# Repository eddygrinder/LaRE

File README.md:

## Objectives
This project is an integral part of the Master’s Dissertation entitled “LaRE – Expandable Remote Laboratory”.
It implements and manages a remote laboratory for electronics education, designed as a viable alternative to VISIR, with the additional commitment of being an open-source project, accessible to any educational institution regardless of geographical location.

The board matrix, the core element of the system, was developed based on a software-controlled architecture independent of proprietary platforms, ensuring that the system can be used without commercial licenses.

However, due to the current lack of support for the pyVirtualBench library on Linux systems and ARM architectures, the implementation of LaRE remains dependent on Windows systems — a factor that limits its adoption in more versatile and low-cost educational platforms.
Nevertheless, the modular architecture of LaRE enables future expansions and adaptations to different pedagogical contexts.

This dissertation partially fulfills the requirements defined in the Course Unit of Dissertation/Thesis of the 2nd year of the Master’s Degree in Electrical and Computer Engineering, specialization area in Automation and Systems.

## System Overview

The LaRE system is composed of:

* **PC (Server)** – runs a Flask-based Python web server.  
* **Raspberry Pi 5** – controls the relay matrix for switching circuits.  
* **NI VirtualBench (VB-8012)** – handles voltage, current, and waveform measurements.  
* **Web Interface** – implemented in HTML, CSS, and JavaScript for user interaction.  

Communication between the PC and Raspberry Pi is handled via **network sockets**, ensuring a simple and robust client–server connection.

## Helpful Resources
Flask base structure simplified and adapted to suit the project’s requirements.
* Some of the Flask features were inspired by a YouTube tutorial, which served as a reference for understanding the basic setup of routes, templates, and frontend communication - https://www.youtube.com/watch?v=dam0GPOAvVI
* https://flask.palletsprojects.com/en/stable/
* The pyVirtualBench library can be found here: https://github.com/armstrap/armstrap-pyvirtualbench
* Additional information: http://armstrap.org/2015/07/27/pyvirtualbench-controlling-five-instruments-from-a-single-python-application/

## Requirements (Windows Only)
* [NI VirtualBench hardware](http://www.ni.com/virtualbench/)
* [VirtualBench driver >= 1.1.0](https://www.ni.com/en-us/support/downloads/drivers/download.virtualbench-software.html#324215)
  Be sure to check "ANSI C Support" during installation.
    
* [Python >= 3.4](https://www.python.org/downloads/).  You will need 32-bit Python support to work with the NI-provided drivers.

## Dependencies
To install the Python dependencies:
* pip install -r requirements.txt

## Licensing
This project is distributed under the terms of the GNU General Public License, version 3 (GPLv3).
It includes portions of code adapted from: armstrap/armstrap-pyvirtualbench, licensed under the MIT License (© 2015 Charles Armstrap).

See the files LICENSE and THIRD_PARTY_LICENSES.txt for full details.

## Author
Eduardo Ramalhadeiro
Master’s in Electrical and Computer Engineering – Automation and Systems
Instituto Politécnico do Porto (ISEP)
© 2025

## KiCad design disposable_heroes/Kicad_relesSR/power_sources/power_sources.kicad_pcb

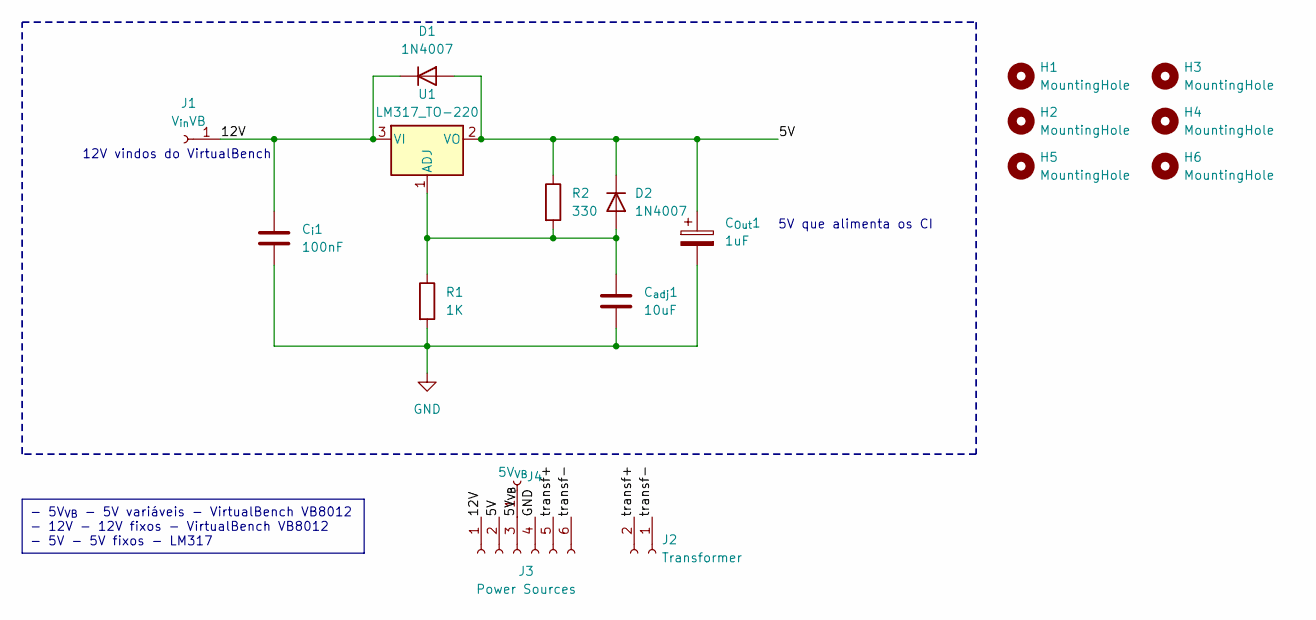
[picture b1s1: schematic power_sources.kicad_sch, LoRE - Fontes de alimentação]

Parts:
C_{Out}1: 1uF; CP_Radial_D5.0mm_P2.00mm
C_{adj}1: 10uF; CP_Radial_D5.0mm_P2.00mm
C_{i}1: 100nF; C_Disc_D5.1mm_W3.2mm_P5.00mm
D1, D2: 1N4007; D_DO-41_SOD81_P10.16mm_Horizontal
H1, H2, H3, H4, H5, H6: MountingHole; MountingHole_3.2mm_M3
J1: V_{in}VB; PinSocket_1x01_P2.54mm_Vertical
J2: Transformer; PinSocket_1x02_P2.54mm_Vertical
J3: Power Sources; PinSocket_1x06_P2.54mm_Vertical
J4: 5V_{VB}; PinSocket_1x01_P2.54mm_Vertical
R1: 1K; R_Axial_DIN0207_L6.3mm_D2.5mm_P15.24mm_Horizontal
R2: 330; R_Axial_DIN0207_L6.3mm_D2.5mm_P15.24mm_Horizontal
U1: LM317_TO-220; TO-220-3_Vertical

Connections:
/5V: C_{Out}1.1, D1.2 (A), D2.1 (K), J3.2, R2.1, U1.2 (VO)
/5V_{VB}: J3.3, J4.1
/12V: C_{i}1.1, D1.1 (K), J1.1, J3.1, U1.3 (VI)
/transf+: J2.2, J3.5
/transf-: J2.1, J3.6
GND: C_{Out}1.2, C_{adj}1.2, C_{i}1.2, J3.4, R1.2
unnamed: C_{adj}1.1, D2.2 (A), R1.1, R2.2, U1.1 (ADJ)

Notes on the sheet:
- 5V_{VB} - 5V variáveis - VirtualBench VB8012 - 12V - 12V fixos - VirtualBench VB8012 - 5V - 5V fixos - LM317
5V que alimenta os CI
12V vindos do VirtualBench

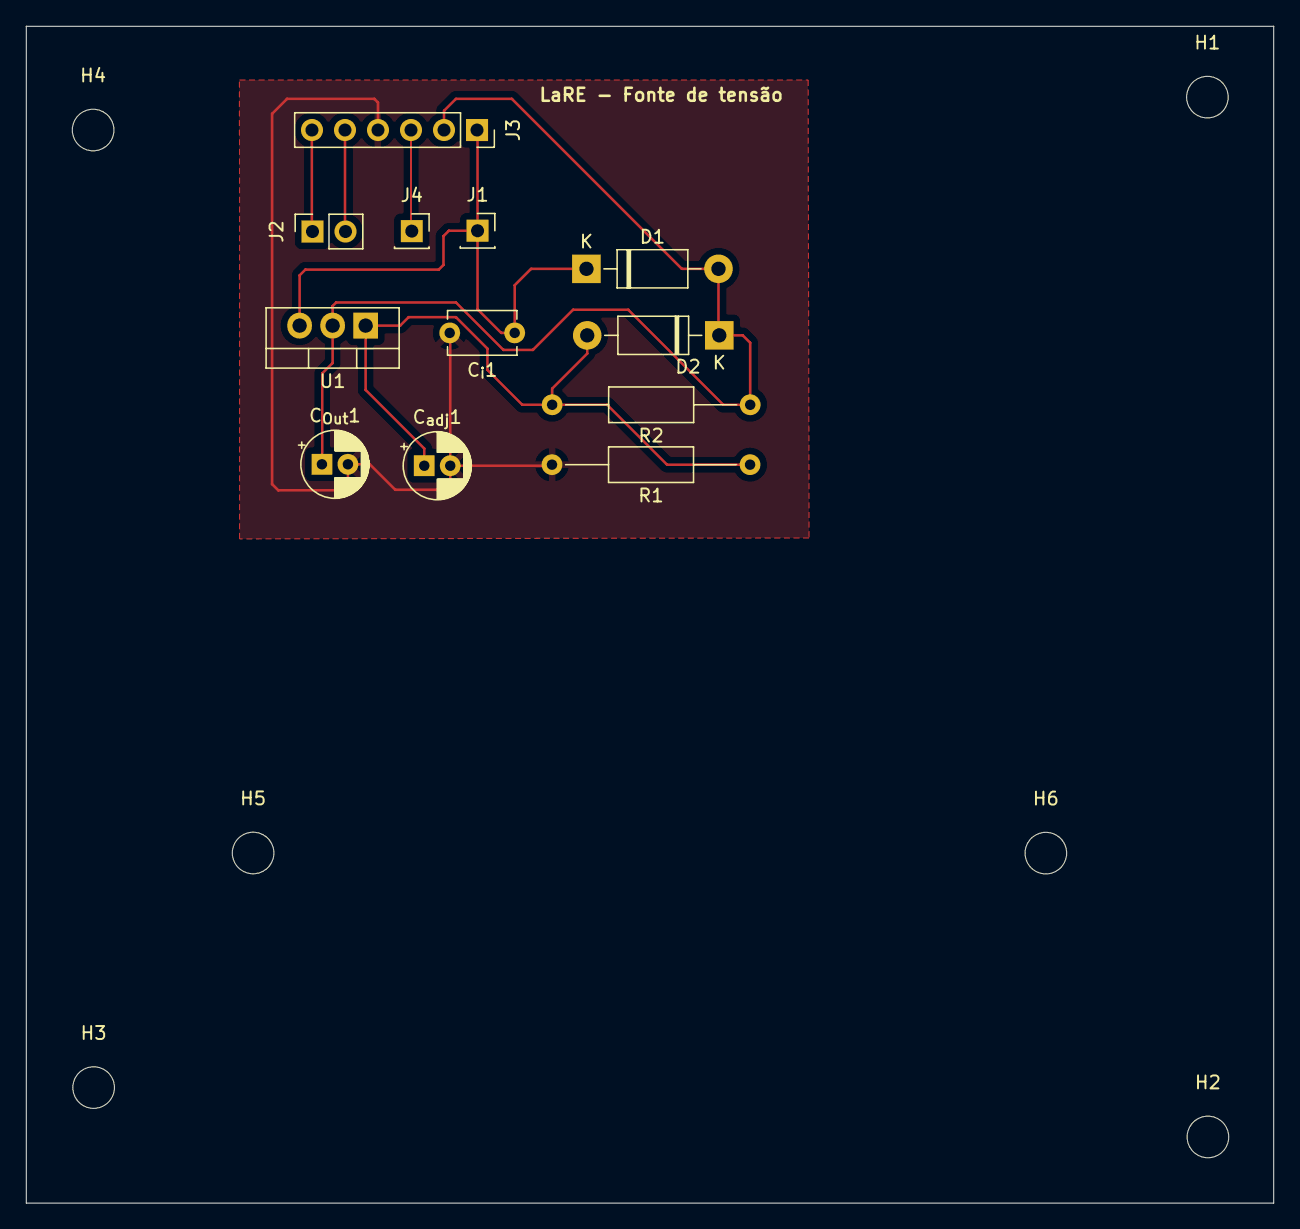
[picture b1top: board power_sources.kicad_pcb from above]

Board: 4 copper layers, 96.0 x 90.6 mm, 18 parts (0 on the bottom side), 7 nets.

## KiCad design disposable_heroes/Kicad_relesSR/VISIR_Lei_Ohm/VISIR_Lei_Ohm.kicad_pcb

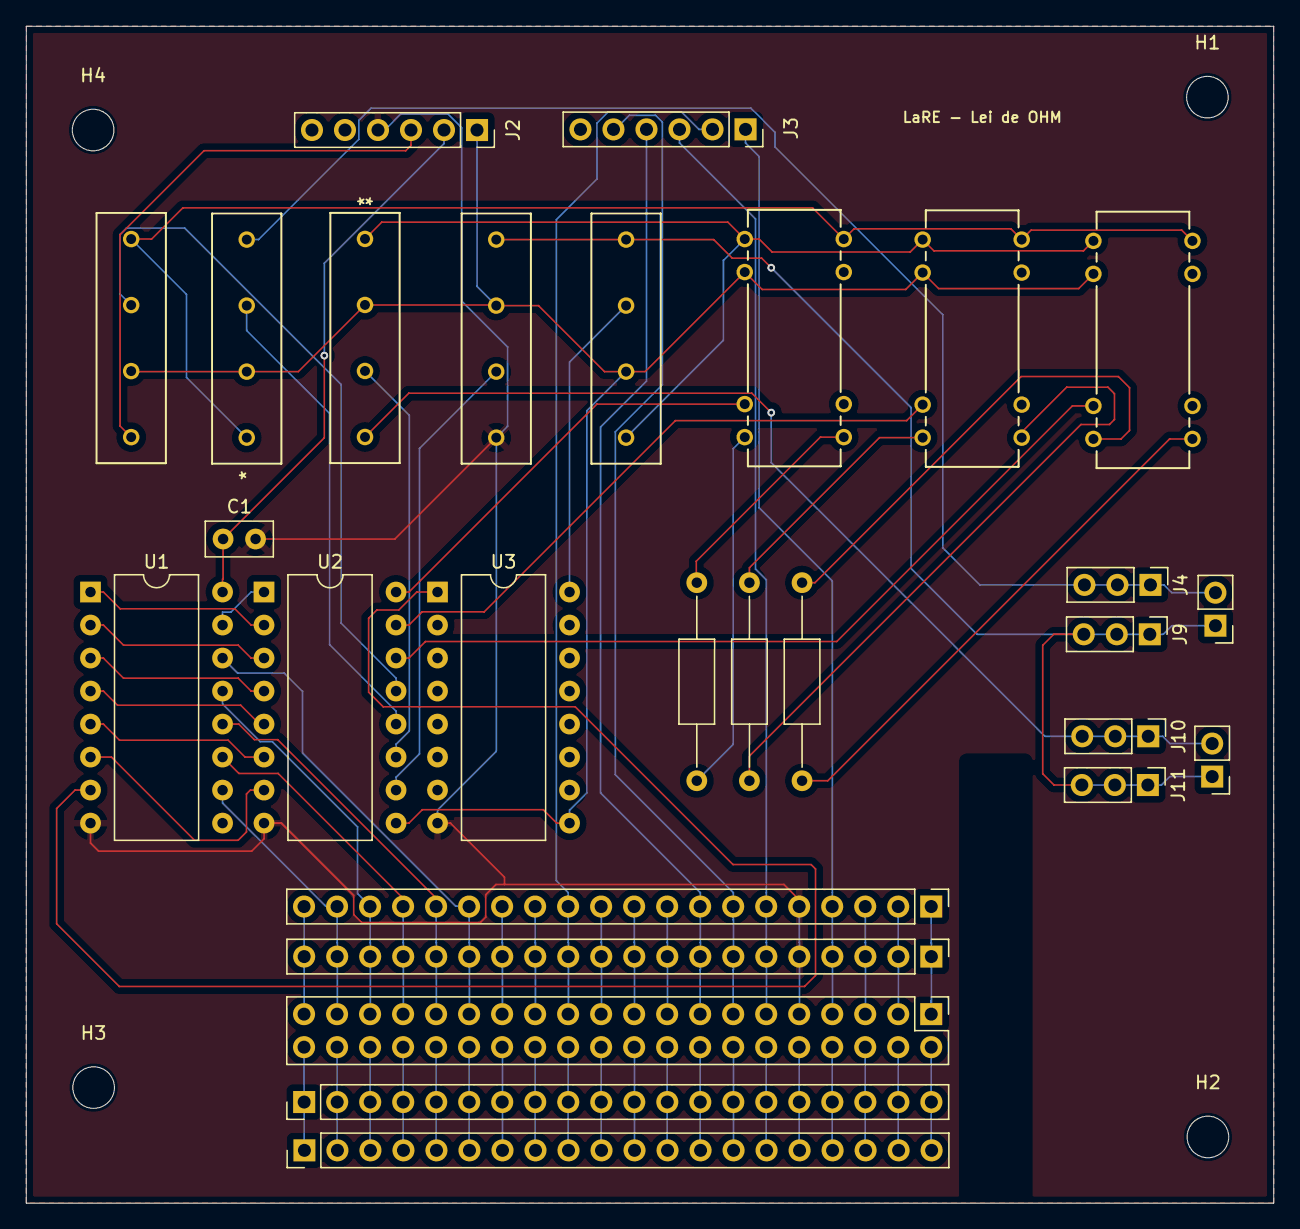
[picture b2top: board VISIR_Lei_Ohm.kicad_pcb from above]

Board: 2 copper layers, 96.0 x 90.5 mm, 32 parts (0 on the bottom side), 70 nets.

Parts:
C1: 0.1uF; C_Disc_D5.0mm_W2.5mm_P2.50mm
H1, H2, H3, H4: MountingHole; MountingHole_3.2mm_M3
J1: Raspberry PI5; PinHeader_2x20_P2.54mm_Vertical
J2: Power Sources; PinSocket_1x06_P2.54mm_Vertical
J3: PI_config; PinSocket_1x06_P2.54mm_Vertical
J4: Voltimetro+; PinHeader_1x03_P2.54mm_Vertical
J5, J6, J7, J8: Ext_OUT_PI; PinHeader_1x20_P2.54mm_Vertical
J9: Voltimetro-; PinHeader_1x03_P2.54mm_Vertical
J10: Amperimetro+; PinHeader_1x03_P2.54mm_Vertical
J11: Amperimetro-; PinHeader_1x03_P2.54mm_Vertical
K1, K2, K3: 3572-1220-123; RELAY8_3572-1220-053_COM
K4, K5, K6, K7, K8: 3570-1331-123; SIP_3570-1331_COM
MES1: Voltmeter_DC; PinHeader_1x02_P2.54mm_Vertical
MES3: Ammeter_DC; PinHeader_1x02_P2.54mm_Vertical
R1: R1; R_Axial_DIN0207_L6.3mm_D2.5mm_P15.24mm_Horizontal
R2: R2; R_Axial_DIN0207_L6.3mm_D2.5mm_P15.24mm_Horizontal
R3: R3; R_Axial_DIN0207_L6.3mm_D2.5mm_P15.24mm_Horizontal
U1: 74HC595N_112; DIP-16_W10.16mm
U2, U3: ULN2003; DIP-16_W10.16mm

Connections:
/5V: C1.1, J2.2, U1.16 (VCC)
/5VPower1: J1.2 (5VPower1), J5.20, J6.20
/5V_{VB}: J2.3, K4.1
/12V: J2.1, K1.2, K2.2, K3.2, K4.2, K5.2, K6.2, K7.2, K8.2, U2.9 (COM), U3.9 (COM)
/I_{11}: U1.15 (Q0), U2.1 (I1)
/I_{12}: U1.1 (Q1), U2.2 (I2)
/I_{13}: U1.2 (Q2), U2.3 (I3)
/I_{14}: U1.3 (Q3), U2.4 (I4)
/I_{15}: U1.4 (Q4), U2.5 (I5)
/I_{16}: U1.5 (Q5), U2.6 (I6)
/I_{17}: U1.6 (Q6), U2.7 (I7)
/I_{21}: U1.7 (Q7), U3.1 (I1)
/O_{11}: K1.6, U2.16 (O1)
/O_{12}: K2.6, U2.15 (O2)
/O_{13}: K3.6, U2.14 (O3)
/O_{14}: K4.3, U2.13 (O4)
/O_{15}: K5.3, U2.12 (O5)
/O_{16}: K6.3, U2.11 (O6)
/O_{17}: K7.3, U2.10 (O7)
/O_{21}: K8.3, U3.16 (O1)
/RCLK: J1.31 (GPIO6), J7.16, J8.16, U1.12 (RCLK)
/RCLK_{filters}: J1.11 (GPIO17), J3.3, J7.6, J8.6
/SER1: J1.29 (GPIO5), J7.15, J8.15, U1.14 (SER)
/SER_{filters}: J1.13 (GPIO27), J3.5, J7.7, J8.7
/SRCLK: J1.33 (GPIO13/PWM1), J7.17, J8.17, U1.11 (SRCLK)
/SRCLK_{filters}: J1.7 (GPIO4/GPCLK0), J3.1, J7.4, J8.4
/~OE: J1.35 (GPIO19/PCM_FS), J7.18, J8.18, U1.13 (~OE)
/~OE_{filters}: J1.15 (GPIO22), J3.4, J7.8, J8.8
/~SRCLR: J1.37 (GPIO26), J7.19, J8.19, U1.10 (~SRCLR)
/~SRCLR_{filters}: J1.23 (GPIO11/SCLK), J3.2, J7.12, J8.12
A: K1.14, K2.14, K3.14, K4.4, K5.1
B: K1.1, K2.1, K3.1, K6.1, K8.1
C: J9.1, J9.2, J9.3, J11.1, J11.2, J11.3, K7.1, K8.4, MES1.1 (-), MES3.1 (-)
GND: C1.2, J1.9 (GND), J2.4, J7.5, J8.5, K7.4, U1.8 (GND), U2.8 (GND), U3.8 (GND)
GND1: J1.25 (GND), J7.13, J8.13
GND2: J1.39 (GND), J7.20, J8.20
GND3: J1.6 (GND), J5.18, J6.18
GND4: J1.14 (GND), J5.14, J6.14
GND5: J1.20 (GND), J5.11, J6.11
GND6: J1.30 (GND), J5.6, J6.6
GND7: J1.34 (GROUND), J5.4, J6.4
unnamed: J1.1 (3V3Power1), J7.1, J8.1
unnamed: J1.17 (3v3Power2), J7.9, J8.9
unnamed: J1.4 (5VPower2), J5.19, J6.19
unnamed: J1.27 (GPIO0/ID_SD), J7.14, J8.14
unnamed: J1.28 (GPIO1/ID_SC), J5.7, J6.7
unnamed: J1.3 (GPIO2/SDA), J7.2, J8.2
unnamed: J1.5 (GPIO3/SCL), J7.3, J8.3
unnamed: J1.26 (GPIO7/CE1), J5.8, J6.8
unnamed: J1.24 (GPIO8/CE0), J5.9, J6.9
unnamed: J1.21 (GPIO9/MISO), J7.11, J8.11
unnamed: J1.19 (GPIO10/MOSI), J7.10, J8.10
unnamed: J1.32 (GPIO12/PWM0), J5.5, J6.5
unnamed: J1.8 (GPIO14/TXD), J5.17, J6.17
unnamed: J1.10 (GPIO15/RXD), J5.16, J6.16
unnamed: J1.36 (GPIO16), J5.3, J6.3
unnamed: J1.12 (GPIO18/PCM_CLK), J5.15, J6.15
unnamed: J1.38 (GPIO20/PCM_DIN), J5.2, J6.2
unnamed: J1.40 (GPIO21/PCM_DOUT), J5.1, J6.1
unnamed: J1.16 (GPIO23), J5.13, J6.13
unnamed: J1.18 (GPIO24), J5.12, J6.12
unnamed: J1.22 (GPIO25), J5.10, J6.10
unnamed: J4.1, J4.2, J4.3, K5.4, MES1.2 (+)
unnamed: J10.1, J10.2, J10.3, K6.4, MES3.2 (+)
unnamed: K1.7, R1.1
unnamed: K1.8, R1.2
unnamed: K2.7, R2.2
unnamed: K2.8, R2.1
unnamed: K3.7, R3.2
unnamed: K3.8, R3.1

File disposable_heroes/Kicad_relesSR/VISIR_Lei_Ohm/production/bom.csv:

Designator,Footprint,Quantity,Value,LCSC Part #
C1,C_Disc_D5.0mm_W2.5mm_P2.50mm,1,0.1uF,
J1,PinHeader_2x20_P2.54mm_Vertical,1,Raspberry PI5,
J10,PinHeader_1x03_P2.54mm_Vertical,1,Amperimetro+,
J11,PinHeader_1x03_P2.54mm_Vertical,1,Amperimetro-,
J2,PinHeader_1x02_P2.54mm_Vertical,1,Fonte dc_VB,
J3,PinHeader_1x02_P2.54mm_Vertical,1,Fonte 12V,
J4,PinHeader_1x03_P2.54mm_Vertical,1,Voltimetro+,
"J5, J6, J7, J8",PinHeader_1x20_P2.54mm_Vertical,4,Ext_OUT_PI,
J9,PinHeader_1x03_P2.54mm_Vertical,1,Voltimetro-,
"K1, K2, K3",RELAY8_3572-1220-053_COM,3,3572-1220-123,
"K4, K5, K6, K7, K8",SIP_3570-1331_COM,5,3570-1331-123,
MES1,PinHeader_1x02_P2.54mm_Vertical,1,Voltmeter_DC,
MES3,PinHeader_1x02_P2.54mm_Vertical,1,Ammeter_DC,
R1,R_Axial_DIN0207_L6.3mm_D2.5mm_P15.24mm_Horizontal,1,R1,
R2,R_Axial_DIN0207_L6.3mm_D2.5mm_P15.24mm_Horizontal,1,R2,
R3,R_Axial_DIN0207_L6.3mm_D2.5mm_P15.24mm_Horizontal,1,R3,
U1,DIP-16_W10.16mm,1,74HC595N_112,"74HC595N,112"
"U2, U3",DIP-16_W10.16mm,2,ULN2003,

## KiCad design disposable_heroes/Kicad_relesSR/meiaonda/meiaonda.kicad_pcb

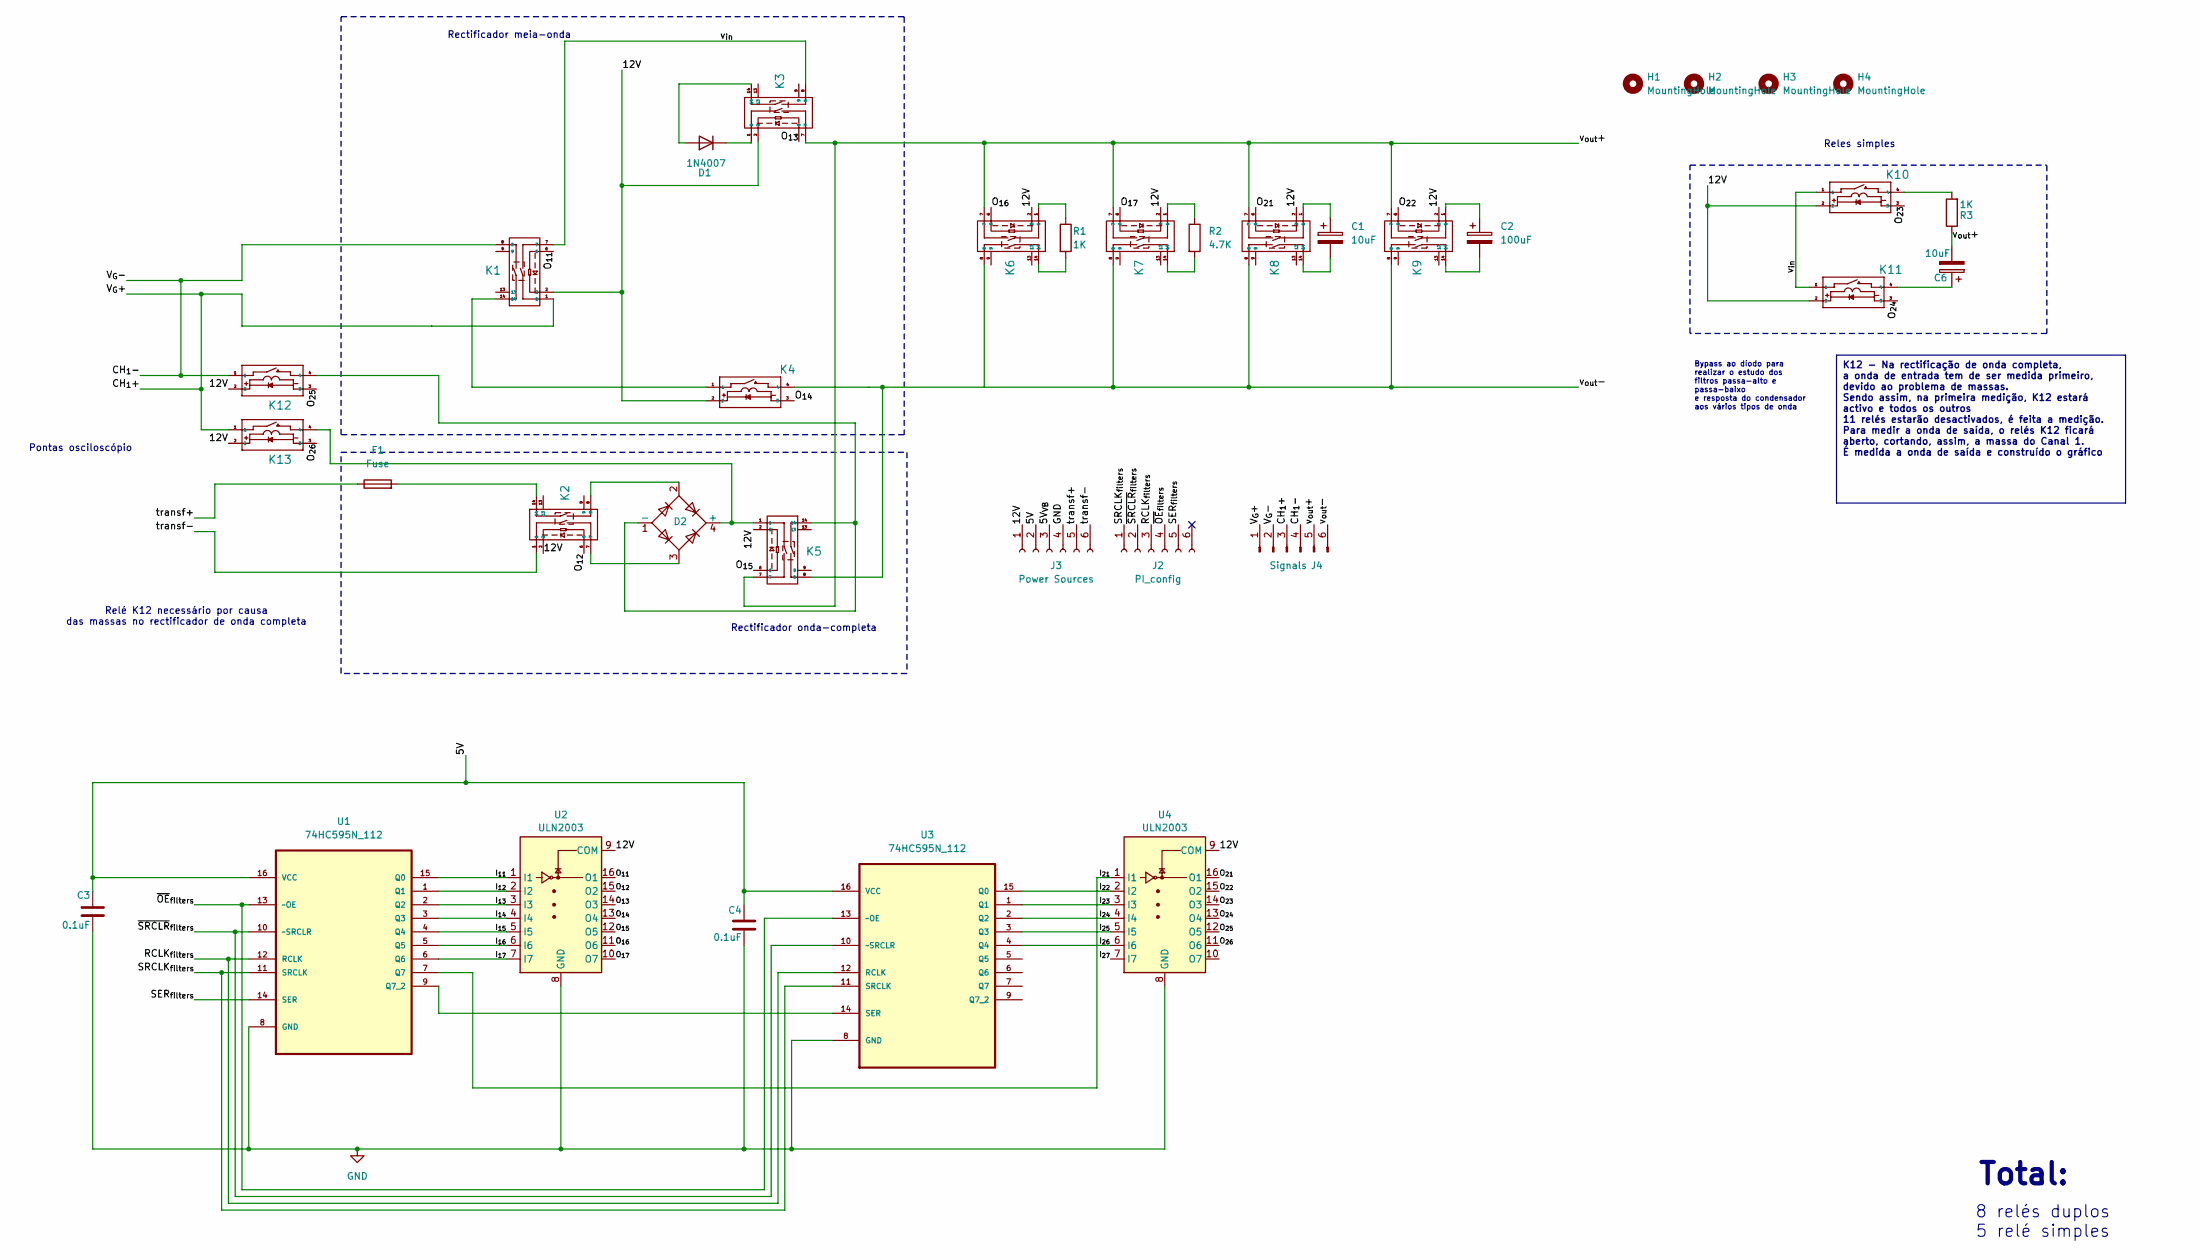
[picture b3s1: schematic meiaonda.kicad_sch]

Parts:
C1: 10uF; CP_Radial_D6.3mm_P2.50mm
C2: 100uF; CP_Radial_D6.3mm_P2.50mm
C3, C4: 0.1uF; C_Disc_D5.0mm_W2.5mm_P2.50mm
C6: 10uF; CP_Radial_D5.0mm_P2.00mm
D1: 1N4007; D_DO-41_SOD81_P10.16mm_Horizontal
D2: B250C2300-1500A; Diode_Bridge_19.0x3.5x10.0mm_P5.0mm
F1: Fuse; Fuseholder_Cylinder-5x20mm_Stelvio-Kontek_PTF78_Horizontal_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
H1, H2, H3, H4: MountingHole; MountingHole_3.2mm_M3
J2: PI_config; PinSocket_1x06_P2.54mm_Vertical
J3: Power Sources; PinSocket_1x06_P2.54mm_Vertical
J4: Signals; PinSocket_1x06_P2.54mm_Vertical
K1, K2, K3, K5, K6, K7, K8, K9: 3572-1220-123; RELAY8_3572-1220-053_COM
K4, K10, K11, K12, K13: 3570-1331-123; SIP_3570-1331_COM
R1, R3: 1K; R_Axial_DIN0207_L6.3mm_D2.5mm_P15.24mm_Horizontal
R2: 4.7K; R_Axial_DIN0207_L6.3mm_D2.5mm_P15.24mm_Horizontal
U1, U3: 74HC595N_112; DIP-16_W10.16mm; MPN 74HC595N,112
U2, U4: ULN2003; DIP-16_W10.16mm

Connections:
/5V: C3.1, C4.1, J3.2, U1.16 (VCC), U3.16 (VCC)
/5V_{VB}: J3.3
/12V: J3.1, K1.2, K2.2, K3.2, K4.2, K5.2, K6.2, K7.2, K8.2, K9.2, K10.2, K11.2, K12.2, K13.2, U2.9 (COM), U4.9 (COM)
/CH_{1}+: J4.1, J4.3, K1.1, K13.1
/CH_{1}-: J4.2, J4.4, K1.8, K12.1
/I_{11}: U1.15 (Q0), U2.1 (I1)
/I_{12}: U1.1 (Q1), U2.2 (I2)
/I_{13}: U1.2 (Q2), U2.3 (I3)
/I_{14}: U1.3 (Q3), U2.4 (I4)
/I_{15}: U1.4 (Q4), U2.5 (I5)
/I_{16}: U1.5 (Q5), U2.6 (I6)
/I_{17}: U1.6 (Q6), U2.7 (I7)
/I_{21}: U1.7 (Q7), U4.1 (I1)
/I_{22}: U3.15 (Q0), U4.2 (I2)
/I_{23}: U3.1 (Q1), U4.3 (I3)
/I_{24}: U3.2 (Q2), U4.4 (I4)
/I_{25}: U3.3 (Q3), U4.5 (I5)
/I_{26}: U3.4 (Q4), U4.6 (I6)
/I_{27}: U4.7 (I7)
/O_{11}: K1.6, U2.16 (O1)
/O_{12}: K2.6, U2.15 (O2)
/O_{13}: K3.6, U2.14 (O3)
/O_{14}: K4.3, U2.13 (O4)
/O_{15}: K5.6, U2.12 (O5)
/O_{16}: K6.6, U2.11 (O6)
/O_{17}: K7.6, U2.10 (O7)
/O_{21}: K8.6, U4.16 (O1)
/O_{22}: K9.6, U4.15 (O2)
/O_{23}: K10.3, U4.14 (O3)
/O_{24}: K11.3, U4.13 (O4)
/O_{25}: K12.3, U4.12 (O5)
/O_{26}: K13.3, U4.11 (O6)
/RCLK_{filters}: J2.3, U1.12 (RCLK), U3.12 (RCLK)
/SER_{filters}: J2.5, U1.14 (SER)
/SRCLK_{filters}: J2.1, U1.11 (SRCLK), U3.11 (SRCLK)
/transf+: F1.1, J3.5
/transf-: J3.6, K2.1
/v_{in}: K1.7, K3.8, K10.1, K11.1
/v_{out}+: C6.2, J4.5, K3.7, K5.7, K6.7, K7.7, K8.7, K9.7, R3.1
/v_{out}-: J4.6, K4.4, K5.8, K7.8, K8.8, K9.8
/~OE_{filters}: J2.4, U1.13 (~OE), U3.13 (~OE)
/~SRCLR_{filters}: J2.2, U1.10 (~SRCLR), U3.10 (~SRCLR)
GND: C3.2, C4.2, J3.4, U1.8 (GND), U2.8 (GND), U3.8 (GND), U4.8 (GND)
unnamed: C1.1, K8.1
unnamed: C1.2, K8.14
unnamed: C2.1, K9.1
unnamed: C2.2, K9.14
unnamed: C6.1, K11.4
unnamed: D1.2 (A), K3.14
unnamed: D1.1 (K), K3.1
unnamed: D2.4 (+), K5.1, K13.4
unnamed: D2.1 (-), K5.14, K12.4
unnamed: D2.2, K2.8
unnamed: D2.3, K2.7
unnamed: F1.2, K2.14
unnamed: K1.14, K4.1
unnamed: K6.1, R1.1
unnamed: K6.14, R1.2
unnamed: K7.1, R2.1
unnamed: K7.14, R2.2
unnamed: K10.4, R3.2
unnamed: U1.9 (Q7_2), U3.14 (SER)

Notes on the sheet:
K12 - Na rectificação de onda completa, a onda de entrada tem de ser medida primeiro, devido ao problema de massas. Sendo assim, na primeira medição, K12 estará activo e todos os outros 11 relés estarão desactivados, é feita a medição. Para medir a onda de saída, o relés K12 ficará aberto, cortando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
Rectificador onda-completa
8 relés duplos 5 relé simples
Relé K12 necessário por causa das massas no rectificador de onda completa
Rectificador meia-onda
Reles simples
Pontas osciloscópio
Total:
Bypass ao díodo para realizar o estudo dos filtros passa-alto e passa-baixo e resposta do condensador aos vários tipos de onda

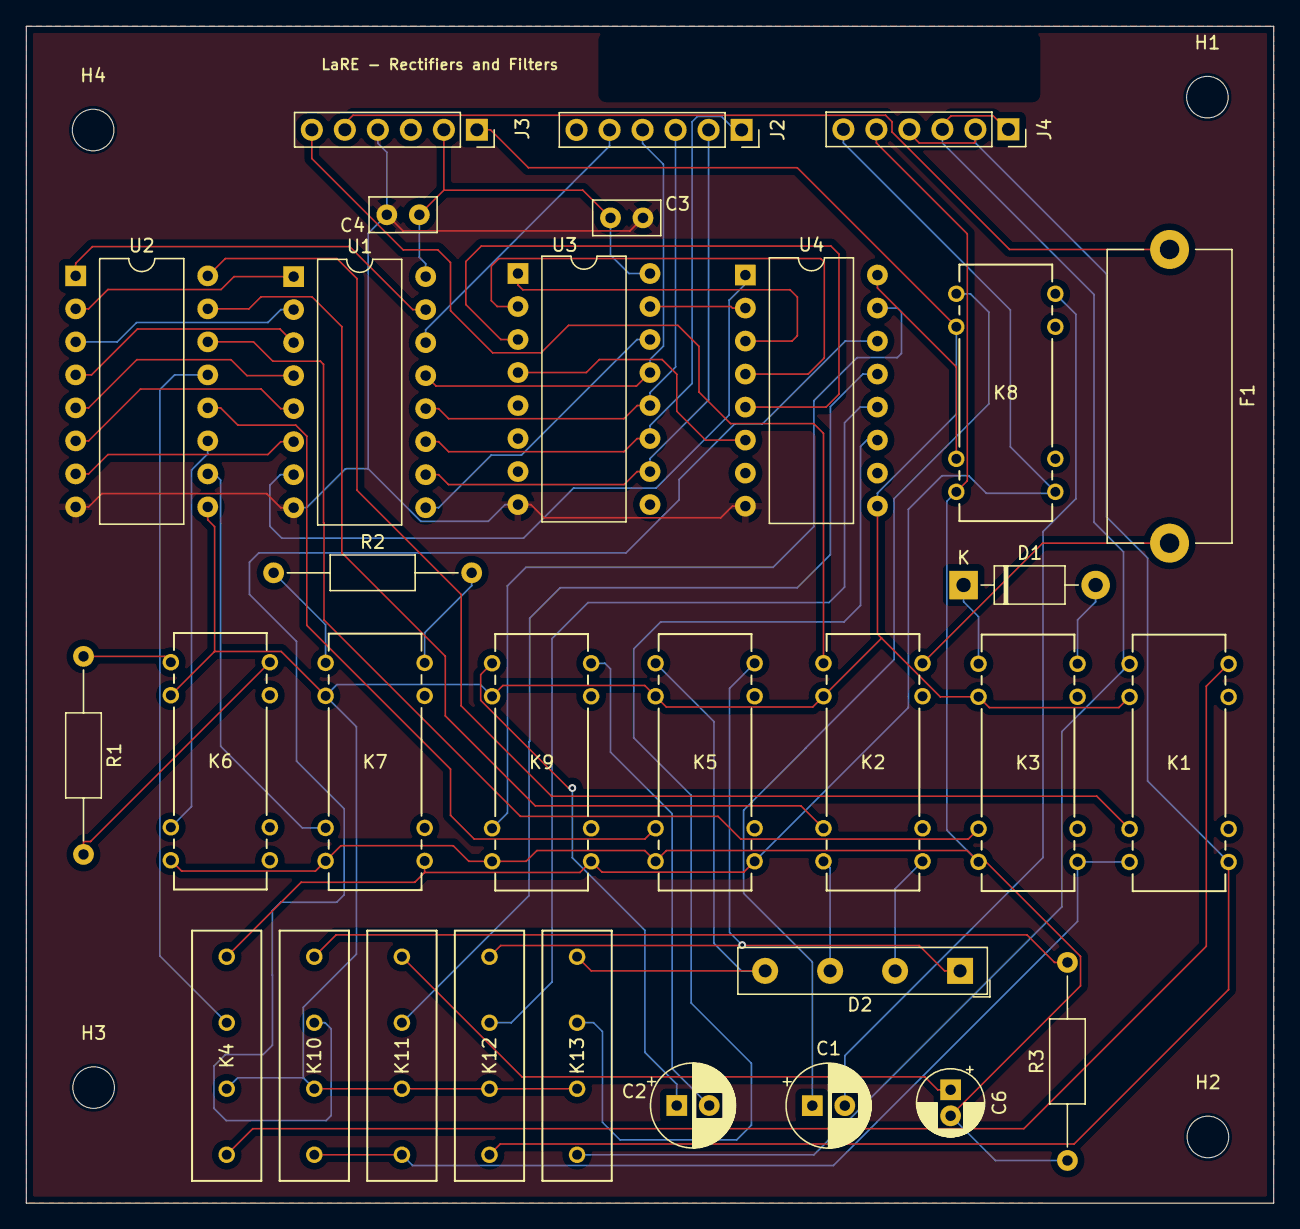
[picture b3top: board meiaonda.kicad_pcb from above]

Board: 2 copper layers, 96.0 x 90.5 mm, 35 parts (0 on the bottom side), 60 nets.

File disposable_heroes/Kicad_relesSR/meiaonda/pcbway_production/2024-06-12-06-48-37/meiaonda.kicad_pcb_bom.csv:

designator,quantity,value,pack,mpn,mount_type
C1,1,10uF,CP_Radial_D6.3mm_P2.50mm,,tht
C2,1,100uF,CP_Radial_D6.3mm_P2.50mm,,tht
"C3, C4",2,0.1uF,C_Disc_D5.0mm_W2.5mm_P2.50mm,,tht
C6,1,10uF,CP_Radial_D5.0mm_P2.00mm,,tht
D1,1,1N4007,D_DO-41_SOD81_P10.16mm_Horizontal,,tht
D2,1,B250C2300-1500A,Diode_Bridge_19.0x3.5x10.0mm_P5.0mm,,tht
F1,1,Fuse,Fuseholder_Cylinder-5x20mm_Stelvio-Kontek_PTF78_Horizontal_Open,,tht
"H1, H2, H3, H4",4,MountingHole,MountingHole_3.2mm_M3,,tht
J2,1,PI_config,PinSocket_1x06_P2.54mm_Vertical,,tht
J3,1,Power Sources,PinSocket_1x06_P2.54mm_Vertical,,tht
J4,1,Signals,PinSocket_1x06_P2.54mm_Vertical,,tht
"K1, K2, K3, K5, K6, K7, K8, K9",8,3572-1220-123,RELAY8_3572-1220-053_COM,,tht
"K10, K11, K12, K13, K4",5,3570-1331-123,SIP_3570-1331_COM,,tht
"R1, R3",2,1K,R_Axial_DIN0207_L6.3mm_D2.5mm_P15.24mm_Horizontal,,tht
R2,1,4.7K,R_Axial_DIN0207_L6.3mm_D2.5mm_P15.24mm_Horizontal,,tht
"U1, U3",2,74HC595N_112,DIP-16_W10.16mm,"74HC595N,112",tht
"U2, U4",2,ULN2003,DIP-16_W10.16mm,,tht

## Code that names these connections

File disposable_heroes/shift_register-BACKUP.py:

import RPi.GPIO as GPIO

#GPIO Mode (BOARD / BCM)
GPIO.setmode(GPIO.BCM)

import serial
import time

import sys
import cv2

import schemdraw
import schemdraw.elements as elm

import subprocess

# Resistencias:
# R1 = 470
# R2 = 1.2K
# R3 = 10K

SER = 5         # GPIO 5 - SER/DS (serial data input, SPI data)
RCLK = 6        # GPIO 6 - RCLK/STCP
SRCLK = 13      # GPIO 13 - SRCLK/SHCP (storage register clock pin, SPI clock)
SRCLR = 26      # GPIO 26 - O registo de deslocamento é limpo (ACTIVO BAIXO)

# Setup dos pinos
GPIO.setup(SER, GPIO.OUT)               
GPIO.setup(RCLK, GPIO.OUT)                     
GPIO.setup(SRCLOCK, GPIO.OUT)
GPIO.setup(SRCLR, GPIO.OUT)

# Inicializar a variavel correspondente a R1
# Reles 1 e 2
rele_1_2 = b0011

# Valor por defeito de espera nas operações do registo de deslocamento
WaitTimeSR = 0.1

# Inicaializa o pino de clear dos registos a 1 - o clear é controlado e feito numa função
GPIO.output(SRCLR, 1)


# Caminho para o visualizador de imagens (pode variar dependendo do seu sistema operacional)
visualizador = "xdg-open"  # Linux
# visualizador = "open"  # macOS
# vi

import warnings
warnings.filterwarnings("ignore")

#arduino = serial.Serial (port='/dev/ttyACM1', baudrate='9600')
#time.sleep(2)

# Caminho para o visualizador de imagens (pode variar dependendo do seu sistema operacional)
visualizador = "xdg-open"  # Linux
# visualizador = "open"  # macOS
# visualizador = "start"  # Windows

def main():
    # Escolha do valor da resistência
    # Não sai do ciclo enquanto não for feita uma escolha válida
    print("Para o estudo da Lei de Ohm escolha uma das três resistências:")
    print("- 470 Ohm")
    print ("- 1.2K")
    print ("- 10K")

    while True:
        try:
            R1_Value = input("Escolha o valor da Resistência - ")

            # Validação da escolha
            if R1_Value in ("470", "1K2", "10K"):
                caminho_imagem = "esquemaOhm.png"
                subprocess.Popen([visualizador, caminho_imagem])
                draw_schematic(R1_Value)
                # Enviar os bits para o Shift register e activar os relés 
                register_clear() # Efectua a limpeza do registo
                SRoutput(rele_1_2)
                break
            else:
                raise ValueError("Escolha não é válida")
        except ValueError as e:
            print(e)    


#if (escolha == 'R1'):
#print("escolheu R1")
#cv2.destroyAllWindows() # destroy all windows
#byte_R1 = "004002000000\n"
#arduino.write(byte_R1.encode())
#time.sleep(0.5)
#arduino.close

def draw_schematic(R1_Value):
    with schemdraw.Drawing(show=False) as d:
        d.config(unit=5) #tamanho do componente
        # Adicionando os elementos
        d += (V1 := elm.SourceV().label('Vin'))
        d += (I1 := elm.MeterA().right().label('Amp'))
        d += elm.Dot()
        d.push()
        d += (R1 := elm.Resistor().down().label(R1_Value, loc='bot'))
        d += elm.Dot()
        d.pop()
        d += (L1 := elm.Line())
        d += (Vol := elm.MeterV().down().label('Volt', loc='bot', rotate=True))
        d += (L2 := elm.Line().tox(V1.start))            
        #d.draw()
        d.save('esquemaOhm.png')

# Funcao que limpa o registo
def register_clear ()
    GPIO.output(SRCLR, 0) # É feito o clear
    time.sleep(waitTimeSR) # espera 100ms
    GPIO.output(SRCLR, 1)

# Função que verifica e desloca os bits para armazenar no registo de deslocamento
def SRoutput(bit_Reles):
    for i in range(4):
        checkshift = shiftnum & 1
        if checkshift == 1:
            WriteReg (checkshift, WaitTimeSR)
        else:
            WriteReg(checkshift, WaitTimeSR)
    shiftnum = shiftnum >> 1


# Definição da função que envia os dados para o registo de deslocamento,
# segundo o algoritmo descrito em baixo

### ALGORITMO ###
# Enviar um bit para o pino SER/DS
### Depois de enviado, é dado um impulso de clock (SRCLK/SHCP) e o bit armazenado nos registos
###### ... um segundo bit é enviado, repetindo os dois passos em cima - É repetido até estarem armazenados 8 bits
######### Por ultimo é dado um impulso aos registos (RCLK/STCP) para obter os 8 bits na saida

def WriteReg (WriteBit, WaitTimeSR):
    GPIO.output (SER,WriteBit) # Envia o bit 1 para o registo
    # Clock - flanco POSITIVO
    time.sleep (WaitTimeSR) # Espera 100ms
    GPIO.output(SRCLK, 0)
    time.sleep (WaitTimeSR) # Espera 100ms
    GPIO.output(SRCLK,1)
    time.sleep(WaitTimeSR) # Espera 100ms
    # Armazenar o valor no registo
    GPIO.output(RCLK, 0)
    time.sleep(WaitTimeSR) # Espera 100ms
    GPIO.output(RCLK, 1)

if __name__ == "__main__":
    main()

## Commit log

2024-03-14 update on calling and including scripts
2024-03-30 update erro "aleatório"
2024-04-03 update: choice and comms not 100%
2024-04-03 update HTML page and CSS file
2024-04-05 update leituras continuas do virtualbench Foi criado um novo arquivo para armazenar as leituras do virtualbench e do dmm, para que seja possível acessar esses valores de qualquer lugar do código.
2024-04-07 Voltage/Current done Graphic interface NOT done
2024-04-09 update numpy graphic
2024-04-11 update graphic
2024-04-15 update - working on graph images
2024-04-27 update kicad
2024-04-29 retificador meia onda
2024-05-04 update meia onda - image
2024-05-07 massive update from laptop to PC
2024-05-08 update kicad meia onda
2024-05-08 update kicad meiaonda e ohm
2024-05-08 cofig func generator
2024-05-09 update meia onda
2024-05-15 update more circuits
2024-05-23 update graph meia onda
2024-05-24 update no grpah
2024-05-24 update graph OK
2024-05-24 grafico meia onda rippple a funcionar
2024-05-28 update error capacitor 74595
2024-05-29 update meia onda funcional, teste onda completa
2024-05-31 update onda completa
2024-06-03 update graph ondacompleta not workig
2024-06-05 problemas com o onda completa
2024-06-05 Rectificador de onda completa a funcionar, somente com o canal 1 ligado à saída, aparentemente, não funciona só com o canal 2
2024-06-06 ONDA COMPLETA A FUNCIONAR
2024-06-06 adiocionado relé K13, para cortar o sinal para a meia onda
2024-06-06 minor update kicad
2024-06-11 start low pass filter
2024-06-11 update reorganize functions and scripts - passalto e passabixo
2024-06-12 update - boards done
2024-06-12 updates finais
2024-06-12 "fim"
2024-06-13 update - 13-06 - all done. Minor changes ahead
2024-07-17 update schematics
2024-07-18 sol_proposta.drawio
2024-07-18 Adicionado Diagrama sem nome.drawio
2024-07-19 Adicionado Diagrama_SOFTWARE.drawio
2024-07-19 Adicionado arquitectura_lare.drawio
2024-07-19 Actualizar Diagrama_SOFTWARE.drawio
2024-07-27 Adicionado flask_folder_Structure.drawio
2024-07-29 Adicionado fluxograma_flask.drawio
2024-07-29 update kicad files
2024-07-29 update home
2024-08-06 Adicionado registo deslocamente.drawio
2024-08-06 Actualizar registo deslocamente.drawio
2024-08-08 Adicionado diagrama_schematic_2003.drawio
2024-08-08 Adicionado func_transmissao_74595.drawio
2024-08-12 Adicionado esquema_simplificado_ohm.drawio
2024-08-13 update esquema simplificado
2024-08-13 Adicionado schematic_OHM.drawio
2024-08-13 Actualizar schematic_OHM.drawio
2024-08-14 Actualizar Diagrama sem nome.drawio
2024-08-14 Actualizar arquitectura_lare.drawio
2024-08-16 Adicionado flowchart_OHM.drawio
2024-08-16 Actualizar flowchart_OHM.drawio
2024-08-17 criação venv
2024-08-20 Adicionado git_diagrama.drawio
2024-08-20 Actualizar git_diagrama.drawio
2024-08-20 Adicionado merda.drawio
2024-08-20 Actualizar ohm_diagrama.drawio
2024-08-20 update: ficheiro diagram, flowchart. Actualização LaRE
2024-10-02 update comentário configVB
2025-01-10 minor update sync
2025-01-19 update esquemas
2025-01-20 minor update
2025-01-20 Update comentários
2025-01-24 update pagina ohm html - instruções, falta fazer a página
2025-02-01 Adicionado circuit_R1.drawio
2025-02-01 Actualizar circuit_R1.drawio
2025-02-01 Adicionado circuit_R1.png
2025-02-03 Adicionado ohm_medidas.drawio
2025-02-03 Actualizar ohm_medidas.drawio
2025-02-04 rearranjo das páginas HTML
2025-02-04 update - uniformização das imagens feitas com o KICAD
2025-02-05 Finished - uniformização paginas HTML
2025-02-05 update ficheiros secundários
2025-02-19 MIINOR update no fich configVB
2025-02-21 minor update - chamada de atenção no ficheiro ohm.html
2025-02-26 add schematic
2025-02-26 added diagrama completo
2025-02-26 del diagramas
2025-02-26 update diagramas
2025-02-27 Adicionado Diagrama_simplificado.drawio
2025-02-27 Actualizar Diagrama_simplificado.drawio
2025-03-13 update ver 2 diagrama software
2025-03-13 Actualizar Diagrama_SOFTWARE_VER2.drawio
2025-03-13 Adicionado Diagrama configVB.drawio
2025-03-14 Adicionado experiencia.drawio
2025-04-14 Adicionado comnicacao_ficheiros.drawio
2025-04-15 Adicionado medicoes_OHM.drawio
2025-04-15 Actualizar medicoes_OHM.drawio
2025-04-16 update images, diagrams
2025-04-16 update grafico
2025-04-16 updatev - gráfico a funcionar correctamente
2025-04-17 update meia onda nao funca
2025-04-17 update ficheiros sistema
2025-04-17 UPDATE IMPORTANTE - rectificação de meia onda está a funcionar, o ficheiro correcto e que NÃO SE DEVE APAGAR é o mixed_signal_osciloscope_FUNCA
2025-04-24 24/04 - tudo aparentemente a funcionar. Falta o rectificador de onda completa e o relé K9 não funciona - ligação entre o registo e o driver. Os nomes dos ficheiros também não estão bem
2025-05-02 update - legendas nos gráficos, coerência nos títulos e apresentação dos valores máximos
2025-05-03 minor updates
2025-05-12 12-05 - Onda completa, funciona somente a onda de saída
2025-05-12 12-05 - aparentemente tudo a funcionar com a onda completa. NO ENTANTO, ainda há problemas de estabilidade no que diz respeito ao gráfico da onda de entrada
2025-06-07 Reles na onda completa têm de ser activados dentro do mixed_signal...
2025-06-12 13-06: software muito instável para medir e apresentar as duas ondas - in e ou. optou-se por medir e apresentar só a saída
2025-06-14 FUNCA
2025-06-14 FUNCA - alguns prints apagados
2025-06-16 UPDATE - O sinal de saída do ripple de onda completa, foi suavizado usando o filtro descrito nos comentários
2025-10-15 UPDATE: passa alto e pasa baixo com informação de espera na visualização do gráfico
2025-10-15 comentários nas páginas HTML
2025-10-15 update main.py com wiatress
2025-10-16 uodate: comentários e readme
2025-10-16 update: comentarios
2025-10-16 Add GNU GPL v3 license file
    Added the GNU General Public License version 3 to the project.
2025-10-16 update cabeçalhos/comentários nos ficheiros
2025-10-17 minor update readme
2025-10-17 minor update - comentário views
2025-10-17 removidos comentários e reduzido tempo para 0.2
2025-10-19 minor UPDATE - CRIAÇÃO DE PÁGINA DE AJUDA ohm.HTML
2025-10-19 final de comentários
